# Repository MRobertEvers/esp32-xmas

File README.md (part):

# ESP32-S3 OSRS Model Renderer

ESP-IDF firmware for an **ESP32-S3** driving a **240×240 ST7789** SPI LCD. It renders an animated Old School RuneScape model in software — no GPU, no PSRAM — using **[toridraw](3rd/oldschool-clientc/3rd/toridraw)** for the raster and **[rscache](3rd/oldschool-clientc/3rd/rscache)** for the cache formats.

The model, its animation, its textures and toridraw's lookup tables are all baked into flash at build time. The device decodes nothing at boot.

Current subject: the Tree Gnome Village spirit tree (dat2 model **2851**) playing `entendseq`, the idle that fades the orbs in its branches.

For experimental relative positioning of four or more ornaments using their
existing Wi-Fi radios, see the [spatial layout module](components/xmas_spatial/README.md)
and [standalone firmware demo](examples/spatial_layout/README.md). The module
implements discovery, FTM ranging and a documented 3D solver without third-party
libraries; it is opt-in and does not start Wi-Fi in the renderer.

---

## Hardware

| LCD pin | GPIO | Notes |
|---------|------|-------|
| SCLK    | 12   | SPI clock — IOMUX pin for SPI2, which is what allows 80 MHz |
| MOSI    | 11   | SPI data — likewise IOMUX |
| CS      | −1   | Tied low on this board |
| DC      | 9    | Data/command |
| RST     | 8    | Reset |
| BLK     | 7    | Backlight, active high, driven by LEDC PWM |
| VCC     | 3.3 V | 3.3 V only |
| GND     | GND  | |

Pins are defined at the top of [`main/main.c`](main/main.c).

**No PSRAM.** It was needed once for toridraw's lookup tables; those are `const` in flash now, and so is the model. Everything left fits in internal DRAM.

### Board (`board/xmas_orn`)

KiCad 10 project.

#### Revision history

| Rev | Date | Module | Power | Outline | Notes |
|-----|------|--------|-------|---------|-------|
| 1 | June 2026 | ESP32-S3-MINI-1-N8 (8 MB flash, no PSRAM) | USB-C only | 27.5 × 39 mm | Ordered as PCBWay SMT quote W1016619ASI9; JLCPCB outputs in `production/` |
| 2 | Sept 2026 | ESP32-S3-WROOM-1-N16R8 (16 MB flash, 8 MB octal PSRAM) | USB-C or 5 V barrel jack, Schottky OR-ed | 27.5 × 41.5 mm | Jack footprint unpopulated; fresh autoroute |

#### Rev 2 changes

- **Module:** ESP32-S3-WROOM-1-N16R8 (16 MB flash, 8 MB octal PSRAM) replaces the
  ESP32-S3-MINI-1-N8. Same GPIOs as above, and none of them are the octal-PSRAM
  pins (35/36/37), so `main.c` is unchanged. The firmware still does not *need*
  PSRAM; `sdkconfig.defaults` keeps the 8 MB flash size so it also boots on rev 1.
  Build with the `sdkconfig.rev2.defaults` overlay for rev 2 boards (see below).
- **Board outline** grew from 27.5 × 39 mm to 27.5 × 41.5 mm; the four mounting
  holes did not move. The module's antenna end overhangs the bottom edge, as the
  MINI-1's did.
- **Power inputs are OR-ed.** USB-C VBUS feeds `VIN` through D3 and the DC jack
  through D4 (B5819W Schottky, SOD-123), so USB and the jack can both be plugged in
  without back-feeding each other. `VIN` goes to the TLV75733 3.3 V LDO as before.
- **J2, DC barrel jack (DC-002, 3.5 × 1.3 mm), not populated.** Footprint and
  3D model live in the project library `xmas_orn.pretty` / `xmas_orn.3dshapes`.
  The jack must be fed **5 V DC** (the LDO's absolute maximum input is 5.5 V);
  the silkscreen says so next to the opening. Pin 1 is the centre pin (`VJACK`),
  pin 2 the sleeve (GND), pin 3 the unused switch contact.
- Copper keep-out rings around the mounting holes; minimum drill lowered to
  0.2 mm for the WROOM-1 thermal vias (within JLCPCB capability).

The routing is a fresh autoroute (Freerouting) that passes DRC with the project
rules, not a hand layout.

Outputs: `board/xmas_orn/docs/` holds the schematic and layer PDFs, a copper/silk
SVG, and 3D renders of both sides
([top](board/xmas_orn/docs/xmas_orn_rev2_top.png),
[bottom](board/xmas_orn/docs/xmas_orn_rev2_bottom.png));
`board/xmas_orn/production/rev2/` holds the JLCPCB gerber/drill zip, BOM and
placement file, exported with `kicad-cli` (J2 excluded as DNP). The placement
rotations are KiCad's raw angles, not the per-package corrections the
Fabrication Toolkit plugin applies, so check the part orientation in JLCPCB's
placement preview before confirming. The files directly under `production/` are
the rev 1 outputs.

Firmware for rev 2: `sdkconfig.rev2.defaults` overlays the 16 MB flash size and
enables the octal PSRAM. The base defaults still build a firmware that runs on
both revisions.

#### Parts on hand for rev 2

The rev 2 part choices follow what was actually bought (from the order emails,
all AliExpress unless noted):

| Part | Qty | Order | Ordered | Used as |
|------|-----|-------|---------|---------|
| ESP32-S3 WROOM-1 family module, N16R8 | 5 | 8212428463925361 | 2026-06-15 | **U1.** Bare module, 16 MB flash + 8 MB PSRAM. The listing photo shows the WROOM-1 shield can; if these turn out to be the 1U (IPEX) variant the same pads apply, only the antenna overhang is unused. |
| DC-002 DC power jack, 3.5 × 1.3 mm, 3-pin | 20 | 8212428463985361 (shipped in package 8212428463965361) | 2026-06-15 | **J2**, not populated by default. Footprint from LCSC C381119 (XKB DC-002-2.0A-1.3); pin 1 centre, 2 sleeve, 3 switch. |
| ESP32-S3-MINI-1-N4R2 | 4 | 8211751284255361 | 2026-06-17 | Not used. Drop-in for the rev 1 MINI-1 footprint (4 MB flash + 2 MB PSRAM) if a rev 1 board is respun instead. |
| ESP32-S3 1.69" touch-screen dev boards | 2 | 8211746880775361 | 2026-06-17 | Not used; dev boards, not modules. |
| ESP-32S (classic ESP32) module set | 1 | 8212349322565361 | 2026-06-17 | Not used; wrong chip family. |
| AYWHP ESP32-S3 dev boards with WROOM-1-N16R8 | 3 | Amazon 114-8171301-3841008 | 2026-06-04 | Not used; dev boards. Handy for bringing up the N16R8 firmware config before rev 2 boards arrive. |
| 3.3 V / 5 V / 12 V power supply module | 1 | 8212428463975361 (same package) | 2026-06-15 | Not on the board. |

#### JLCPCB placement gotchas (learned on order W2026090908054344, 2026-09-08)

- **Rotations.** `kicad-cli` writes KiCad's raw footprint angle, but JLCPCB
  applies that angle to *its own* part model, whose 0° differs per package.
  On the first rev 2 order the 1×7 socket J1 came out vertical and the
  WROOM-1 U1 was flipped end-for-end (antenna on the board, shield hanging
  off the edge). JLCPCB's engineer corrected both before production, and the
  CPL in `production/rev2/` now carries the JLCPCB-correct angles for those
  two parts (J1 = 0, U1 = 0). Any new footprint needs the same check.
- **Always open Order History → DFM Analysis after paying** and tick
  "Show Components": that view is the engineer-adjusted placement that will
  actually be built. Verify every polarised part (diodes, LEDs, ICs, the
  module, connectors) against `docs/xmas_orn_rev2_top.png` before the SMT
  line starts. "Confirm Parts Placement" at order time makes JLCPCB wait for
  your sign-off instead.
- **Through-hole parts must be in the CPL** or JLCPCB skips them: the hub's
  jack, terminal blocks and bulk cap were missing from the SMD-only export.
  `xmas_hub/production/JLCPCB_xmas_hub_positions.csv` now lists all 60 parts
  in the five-column form (Designator, Mid X, Mid Y, Rotation, Layer);
  JLCPCB's parser rejects quoted fields, so keep footprint names out of it.
- **Part numbers.** Give JLCPCB LCSC C-numbers, not manufacturer numbers; its
  matcher fails on hyphenated MPNs. Substitutions made on that order: hub Q1
  AOD417 → AOD4185 (C400894, out of stock); ornament J1 = C22438157,
  J3 = C165948, SW1/SW2 = C231329.

#### Sourcing the rest

Everything new on rev 2 now carries an `LCSC Part #` field in the schematic and
board so an assembler can pick it up directly:

| Ref | Part | LCSC / JLCPCB | Status |
|-----|------|---------------|--------|
| U1 | ESP32-S3-WROOM-1-N16R8 | [C2913202](https://www.lcsc.com/product-detail/C2913202.html) ([DigiKey 16162642](https://www.digikey.com/en/products/detail/espressif-systems/ESP32-S3-WROOM-1-N16R8/16162642)) | 5 on hand |
| J2 | DC-002 jack (XKB DC-002-2.0A-1.3) | [C381119](https://www.lcsc.com/product-detail/C381119.html) | 20 on hand; not populated |
| D3, D4 | B5819W SL, 1 A / 40 V Schottky, SOD-123 | [C8598](https://jlcpcb.com/partdetail/9093-B5819WSL/C8598), a JLCPCB *basic* part | **Not on hand.** Needs 2 per board. |

B5819W was not in any order. It is sourced from JLCPCB's parts library as
[C8598](https://jlcpcb.com/partdetail/9093-B5819WSL/C8598) (Jiangsu Changjing
B5819W SL), a *basic* library part, so it is placed at assembly with no feeder
fee and nothing needs to be bought separately.

Nothing else on the rev 2 BOM changed from rev 1, so the rev 1 part numbers in
`production/JLCPCB_xmas_orn_bom.csv` still apply to those references.

---

### Enclosure (`board/xmas_orn/enclosure`)

A printed case for the rev 2 board plus its display, done as a **common core** (tray + snap-on
bezel) that slots into interchangeable **outers**, the default being a rounded hanging sleeve.
Parametric OpenSCAD, print-oriented STLs for the Bambu Lab A1 mini, and the core envelope /
groove interface any new outer needs are documented in
[board/xmas_orn/enclosure/README.md](board/xmas_orn/enclosure/README.md). The barrel jack and
USB-C are open through both the core and the sleeve.
Five themed outers (Captain America shield, two Spider-Man variants, Iron Man, Black Widow)
share the same pocket and export one STL per colour for the AMS lite.

The power hub gets a plainer two-part box, same toolchain, in
[board/xmas_hub/enclosure/](board/xmas_hub/enclosure/README.md): four M3 screws from below
clamp the board and the lid together, with a notch for the 12 V jack and windows for the four
arm terminals.

---

### Power hub (`board/xmas_hub`)

A second KiCad 10 project: the base-of-tree distribution board for the rev 2
jack. A 12 V / 3 A barrel supply goes in; four independently regulated and
fused **5 V / 3 A arms** come out on screw terminals, each feeding a short
cluster of ornaments through their DC-002 jacks. One TPS54302 buck and one PTC
per arm, so a fault on one arm leaves the other three running — the "star"
topology without a buck on every ornament. Design notes, BOM with LCSC numbers,
cable guidance and the generator scripts are in
[`board/xmas_hub/README.md`](board/xmas_hub/README.md); JLCPCB outputs in
`board/xmas_hub/production/`.

## Software used

| Area | Tool | Version / where | Used for |
|------|------|-----------------|----------|
| Firmware | [ESP-IDF](https://docs.espressif.com/projects/esp-idf/) | v5.1+ | `idf.py` build, flash, monitor; CMake drives the bake generators |
| Firmware | Host C compiler | any `gcc` on `PATH` (`HOST_CC` overrides) | Builds `tools/bake_model` and `tools/extract_model`, which run at build time |
| Firmware | PowerShell | `scripts/*.ps1` | The three build-time generators (`bake-model`, `gen-const-tables`, `extract-model`) |
| Firmware | [toridraw / rscache](https://github.com/MRobertEvers/oldschool-clientc) | submodule pin in `3rd/` | Software rasteriser and OSRS cache readers |
| Board | [KiCad](https://www.kicad.org/) | 10.0.6 | `board/xmas_orn` and `board/xmas_hub` schematics and layouts |
| Board | `kicad-cli` | ships with KiCad | ERC/DRC, netlist, BOM, position file, gerber/drill export, PDF/SVG/PNG renders in `docs/` |
| Board | KiCad's bundled Python (`pcbnew`) | inside the KiCad app bundle | `board/xmas_hub/scripts/gen_sch.py` / `gen_pcb.py` generate that board programmatically |
| Board | [Freerouting](https://github.com/freerouting/freerouting) | | Autorouting; both boards are fresh autoroutes that pass the project DRC |
| Board | [Fabrication Toolkit](https://github.com/bennymeg/Fabrication-Toolkit) | KiCad plugin, `fabrication-toolkit-options.json` | Rev 1 JLCPCB outputs under `production/`; rev 2 used `kicad-cli` directly |
| Enclosure | [OpenSCAD](https://openscad.org/) | 2026.09 snapshot, `brew install --cask openscad@snapshot` | `board/xmas_orn/enclosure/xmas_orn_case.scad`; `export.sh` renders the STLs and the `check_*` parts prove the fit |
| Enclosure | [trimesh](https://trimesh.org/) (optional) | `pip install trimesh numpy networkx` | Watertightness and overlap-volume checks on the exported meshes |
| Enclosure | [Bambu Studio](https://bambulab.com/en/download/studio) | | Slicing for the Bambu Lab A1 mini; the STLs are already print-oriented |

On macOS the stable `openscad` cask is disabled (Gatekeeper); use the snapshot cask. KiCad's
`kicad-cli` and Python live at `/Applications/KiCad/KiCad.app/Contents/MacOS/kicad-cli` and
`.../Contents/Frameworks/Python.framework/Versions/Current/bin/python3`. `qlmanage -t` is a
handy stand-in for `pdftoppm` when previewing the exported PDFs.

## Prerequisites

- ESP-IDF v5.1+
- A host `gcc` on `PATH` (MinGW is fine) to build the bake tools. `HOST_CC` overrides.
- **The OSRS caches**, which are *not* vendored — see below.

### Libraries: vendored as a submodule

`toridraw`, `rscache` and `toridraw_rscache` come from
[`oldschool-clientc`](https://github.com/MRobertEvers/oldschool-clientc), pinned
as a submodule at [`3rd/oldschool-clientc`](3rd/oldschool-clientc).

```powershell
git clone git@github.com:MRobertEvers/esp32-xmas.git
cd esp32-xmas
git submodule update --init --recursive
```

`--recursive` matters: the nested `OSRS-Content` submodule supplies `all.seq`,
which is where the animation frame ids and their hold times come from.

This used to be `../oldschool-clientc` — whatever happened to be checked out
next to this repo on the machine doing the build. That is not a version. The
Xtensa raster kernels this client depends on are developed in that repo, so two
working copies routinely meant two different firmwares from the same source
tree, with nothing recording the difference.

To build against a live working copy of the library instead of the pin:

```powershell
idf.py -DCLIENTC_DIR=C:\path\to\oldschool-clientc build
```

### Caches: local, not vendored

The caches are gigabytes of game data and are gitignored in *both* repos, so the
submodule carries the libraries and the configs but **no cache**. They get their
own root, defaulting to a sibling checkout:

| Variable | Default | |
|---|---|---|
| `CACHE_ROOT` | `../oldschool-clientc` | where the caches live |
| `ANIM_CACHE_DIR` | `${CACHE_ROOT}/cache.osrs239` | dat2 cache |
| `CACHE_DIR` | `${CACHE_ROOT}/cache.rs289lc` | dat1 cache |

Pointing these at the submodule would look tidier and would silently break every
fresh clone, because the directory exists and is empty.

## Build and flash

```powershell
. C:\Users\<you>\esp\esp-idf\export.ps1
idf.py set-target esp32s3
idf.py build
idf.py -p COM3 flash monitor
```

`idf.py build` runs three generators before compiling:

1. **`scripts/bake-model.ps1`** → `build/gen/xmas_baked.c`. The model, the rig, every animation frame and every texture, as `const` arrays.
2. **`scripts/gen-const-tables.ps1`** → `build/gen/toridraw_tables_precomputed.c`. toridraw's HSL palette and trigonometry, for the configured pixel format.
3. **`scripts/extract-model.ps1`** → `build/model.bin`, flashed to the `model` partition.

All three track their CMake cache variables, so changing the model re-bakes.

---

## Choosing a model and animation

```powershell
idf.py -DANIM_MODEL=2851 -DANIM_SEQ=entendseq build
```

| Variable | Default | Meaning |
|---|---|---|
| `ANIM_MODEL` | `2851` | dat2 model id |
| `ANIM_SEQ` | `entendseq` | sequence name in `all.seq` |
| `ANIM_CACHE_DIR` | `${CACHE_ROOT}/cache.osrs239` | dat2 cache |

### Pick a sequence that actually animates this model

Some sequences drive **two** models and hide whichever is not current, by collapsing every one of its vertices onto a single point. Render one model of such a pair and roughly half the frames draw nothing at all — which looks like flicker, and is the animation behaving correctly.

`pog_spirit_tree_anim` is one of these: `models=49769,49771`, cross-faded by `pog_spirit_tree_transform`. 48 of its 99 poses came out with bounds `radius 0`.

The firmware checks for this at boot and says so:

```
all 12 poses draw
```

or, if you have picked one of those sequences:

```
W: 48 of 99 poses draw nothing -- the sequence probably drives a
   second model that this one is hidden for
```

A `readyanim` has no partner: it loops, and every frame has geometry.

### A sequence can hide part of a model on purpose

Picking a sequence that animates the model is not the same as picking one that
shows all of it. Model 2851 has two idles, and `all.loc` uses them to mean
different things:

| loc | anim | orbs |
|---|---|---|
| `spirittree_big_2ops` | `entready` | hidden |
| `spirittree_big_2ops_orbs` | `entendseq` | fading |

The rig has two type-5 (transparency) groups. `entready` holds them at a
constant +16 and +32 on every frame -- and +32x8 = 256, which clamps to 255,
so the orbs are fully hidden. That is correct: that loc has no orbs.
`entendseq` ramps the second group 20 -> 6 and back and dips the first to -10,
which is the fade.

So "the orbs do not fade" had two different causes in sequence, and only the
first was a bug: the model had no face bones baked, so no type-5 op ran at all;
and then the sequence in use genuinely asked for them to be hidden.

---

## Lighting

Applied at bake time, so the device receives finished colours and never lights anything.

```
lightness = ambient + (L·N) / (attenuation × face_count)
```

That result then *scales* each face's own base lightness, clamped to `[2,126]`.

| Variable | Default | Effect |
|---|---|---|
| `LIGHT_AMBIENT` | `128` | The floor. Slides the whole model brighter or darker. |
| `LIGHT_ATTENUATION` | `192` | **The contrast knob.** Divides the directional term, so *lower* is a wider swing. Reference is 768. |
| `LIGHT_GAMMA` | `1.0` | Re-curves the distribution. A **brightness** knob — see below. |
| `LIGHT_DIR` | `-50,-10,-50` | Light vector. |

Every bake prints what it did:

```
lighting: ambient 128, attenuation 192, dir -50,-10,-50
  p10 15, p50 35, p90 120 (inner spread 105)
  lightness 2..126 (spread 124), mean 49, 7% on the clamps
```

**Read the inner spread, not the range.** The min and max are two faces; p10–p90 is the thousand in between, and that is what the eye reads as contrast. Measured on model 2851:

| ambient | attenuation | gamma | inner spread | mean | clipped |
|---|---|---|---|---|---|
| 64 | 768 (reference) | 1.0 | — | 24 | 0% |
| 96 | 384 | 1.0 | 69 | 37 | 0% |
| 96 | 192 | 1.0 | 88 | 38 | 2% |
| 96 | 192 | 0.8 | 87 | 46 | 2% |
| **128** | **192** | **1.0** | **105** | **49** | **7%** |
| 96 | 128 | 1.0 | 108 | 39 | 17% |

`attenuation` is the only knob that moves the inner spread. **Gamma does not add contrast** — measured, it moved the mean 37 → 73 while *shrinking* inner spread 69 → 55. It is there for a model that is too dark, not one that is too flat.

`clipped` is the share of face corners pinned at 2 or 126, which have lost their shading. 7% is the price of the current default; `-DLIGHT_AMBIENT=96 -DLIGHT_ATTENUATION=192 -DLIGHT_GAMMA=0.8` is the same contrast at 2%.

---

## Animation timing

Sequences run on the reference client's **50 Hz** cycle, and each frame carries its own hold time.

That hold time lives **only in the seq config** — `frame=<packed id>,<ticks>` in `all.seq`. The frame archive does not carry it, so nothing downstream can recover it if the packer drops it. `entendseq` holds its 18 frames for 4-5 ticks: about 90 ms a pose. (`entready`, the other idle for this rig, holds for 21.)

The render loop derives the animation phase from `esp_timer` rather than counting passes, so playback rate does not change when render cost does. The boot log reports a measured rate:

```
frame 4: 44.2 fps, 2.0 poses/s  visible=1  7794 px  anim 1.06 ms  raster 5.74 ms  blit 0.25 ms
```

Both numbers are per wall-clock second. Counting frames and multiplying by an assumed period produces a rate that lies whenever the loop misses its period.

---

## Textures

A textured face carries a texture **id**, not texels, and toridraw's texture map starts empty. **Its raster silently skips any face whose id is not registered** — no error, no gap in the depth order. An unregistered texture is indistinguishable from a model with no textured faces.

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
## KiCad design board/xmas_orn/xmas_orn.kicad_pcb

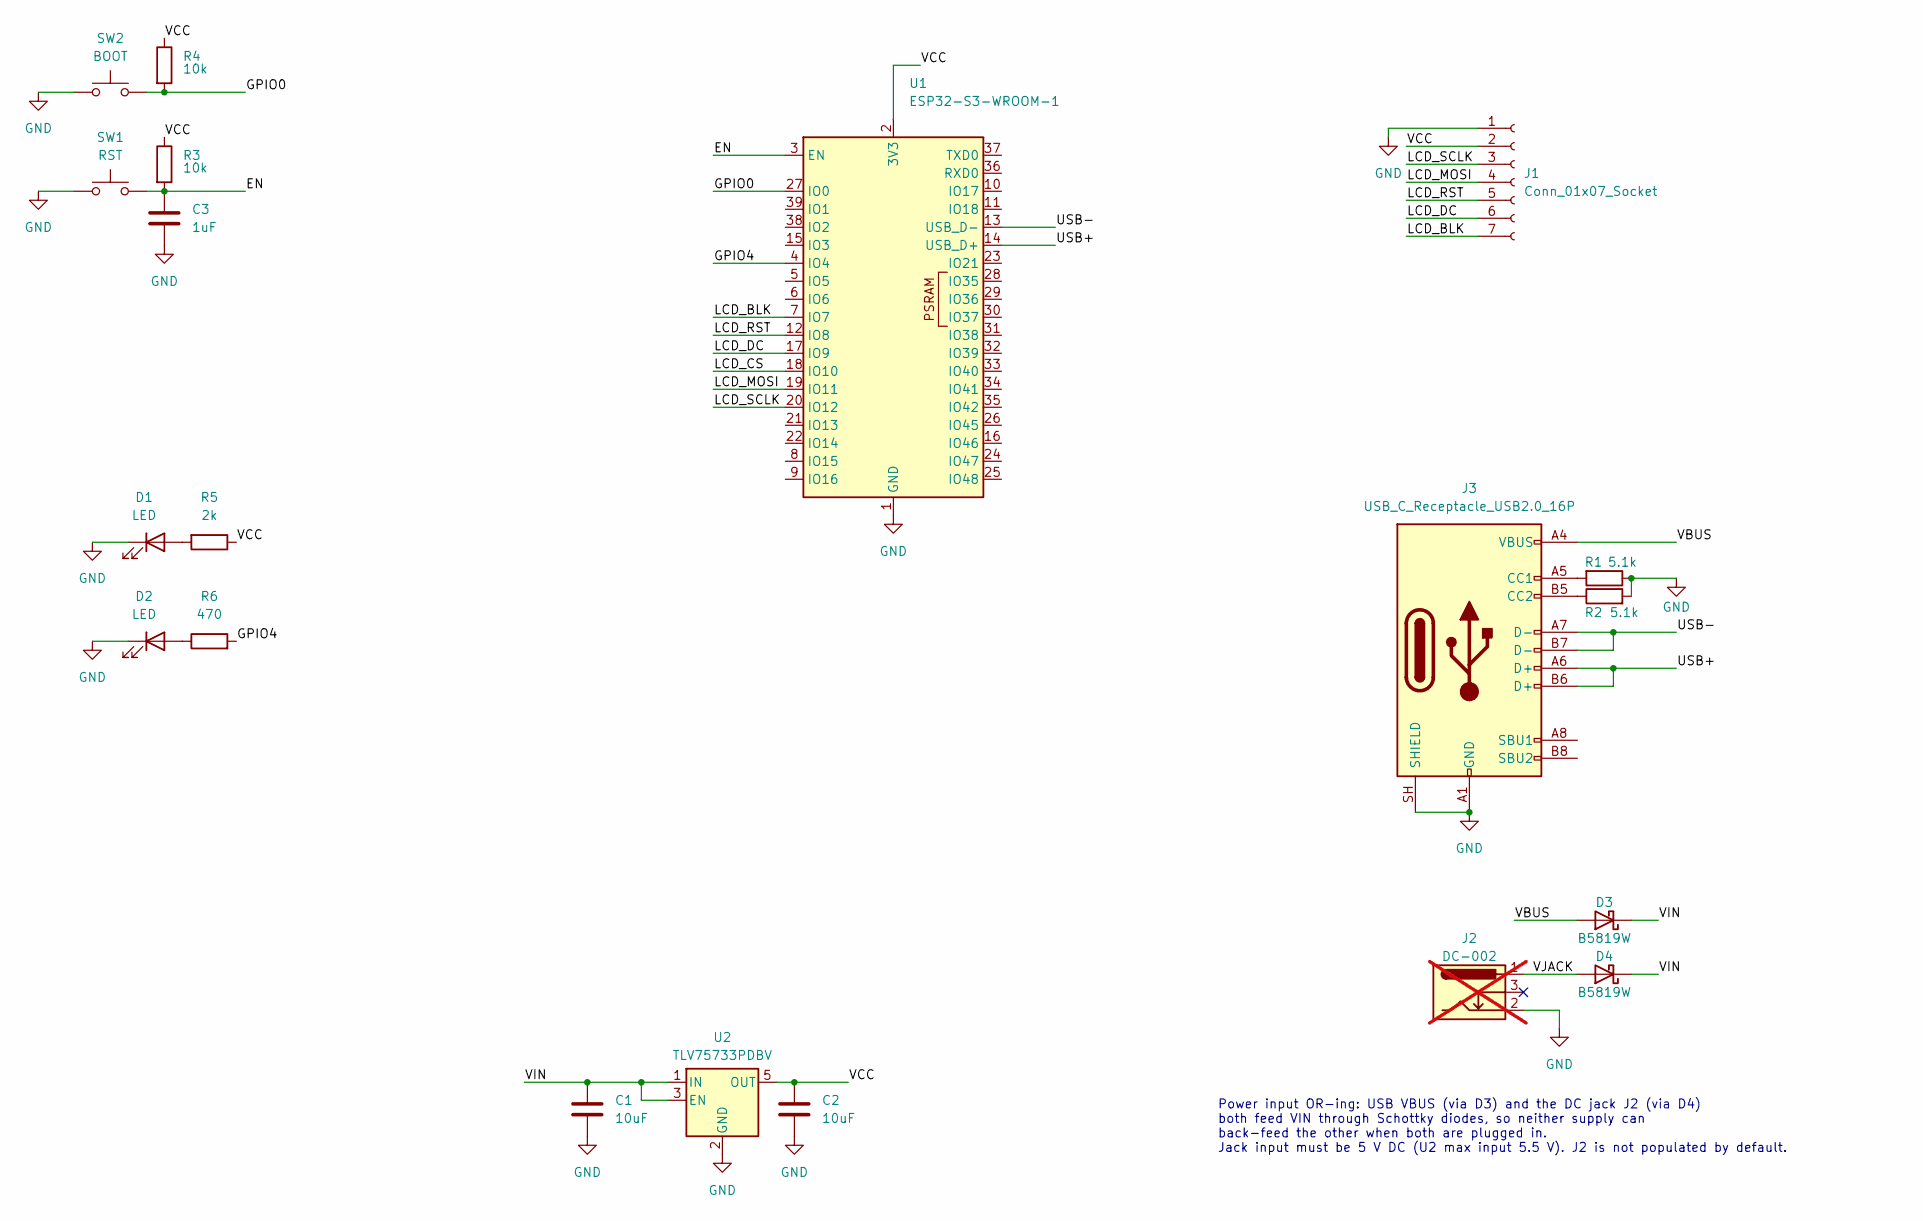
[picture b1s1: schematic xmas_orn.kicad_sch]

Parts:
C1, C2: 10uF; C_0805_2012Metric; MPN CL21A106KOQNNNE
C3: 1uF; C_0603_1608Metric; MPN CL10A105KA8NNNC
D1, D2: LED; LED_0603_1608Metric; MPN 19-217/R6C-AL1M2VY/6T
D3, D4: B5819W; D_SOD-123; MPN B5819W; LCSC Part # C8598
J1: Conn_01x07_Socket; PinSocket_1x07_P2.54mm_Vertical; MPN HX PM2.54-1x7P ZC-Y
J2: DC-002; DC-002_BarrelJack_3.5x1.3mm_Horizontal; MPN DC-002; LCSC Part # C381119; not fitted
J3: USB_C_Receptacle_USB2.0_16P; USB_C_Receptacle_HRO_TYPE-C-31-M-12; MPN TYPE-C-31-M-12
R1, R2: 5.1k; R_0603_1608Metric; MPN RC0603FR-075K1L
R3, R4: 10k; R_0603_1608Metric; MPN AC0603JR-0710KL
R5: 2k; R_0603_1608Metric; MPN RC0603JR-072KL
R6: 470; R_0603_1608Metric; MPN RC0603FR-07470RL
SW1: RST; SW_SPST_B3U-1000P; MPN B3U-1000P
SW2: BOOT; SW_SPST_B3U-1000P; MPN B3U-1000P
U1: ESP32-S3-WROOM-1; MPN ESP32-S3-WROOM-1-N16R8; LCSC Part # C2913202
U2: TLV75733PDBV; SOT-23-5; MPN TLV75733PDBVR-MS

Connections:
/EN: C3.1, R3.2, SW1.2, U1.3 (EN)
/GPIO0: R4.2, SW2.2, U1.27 (IO0)
/GPIO4: R6.2, U1.4 (IO4)
/LCD_BLK: J1.7, U1.7 (IO7)
/LCD_CS: U1.18 (IO10)
/LCD_DC: J1.6, U1.17 (IO9)
/LCD_MOSI: J1.4, U1.19 (IO11)
/LCD_RST: J1.5, U1.12 (IO8)
/LCD_SCLK: J1.3, U1.20 (IO12)
/USB+: J3.A6 (D+), J3.B6 (D+), U1.14 (USB_D+)
/USB-: J3.A7 (D-), J3.B7 (D-), U1.13 (USB_D-)
/VBUS: D3.2 (A), J3.A4 (VBUS), J3.A9 (VBUS), J3.B4 (VBUS), J3.B9 (VBUS)
/VCC: C2.1, J1.2, R3.1, R4.1, R5.1, U1.2 (3V3), U2.5 (OUT)
/VIN: C1.1, D3.1 (K), D4.1 (K), U2.1 (IN), U2.3 (EN)
/VJACK: D4.2 (A), J2.1
GND: C1.2, C2.2, C3.2, D1.1 (K), D2.1 (K), J1.1, J2.2, J3.A1 (GND), J3.A12 (GND), J3.B1 (GND), J3.B12 (GND), J3.SH (SHIELD), R1.1, R2.2, SW1.1, SW2.1, U1.1 (GND), U1.40 (GND), U1.41 (GND), U2.2 (GND)
unnamed: D1.2 (A), R5.2
unnamed: D2.2 (A), R6.1
unnamed: J3.A5 (CC1), R1.2
unnamed: J3.B5 (CC2), R2.1

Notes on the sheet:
Power input OR-ing: USB VBUS (via D3) and the DC jack J2 (via D4) both feed VIN through Schottky diodes, so neither supply can back-feed the other when both are plugged in. Jack input must be 5 V DC (U2 max input 5.5 V). J2 is not populated by default.

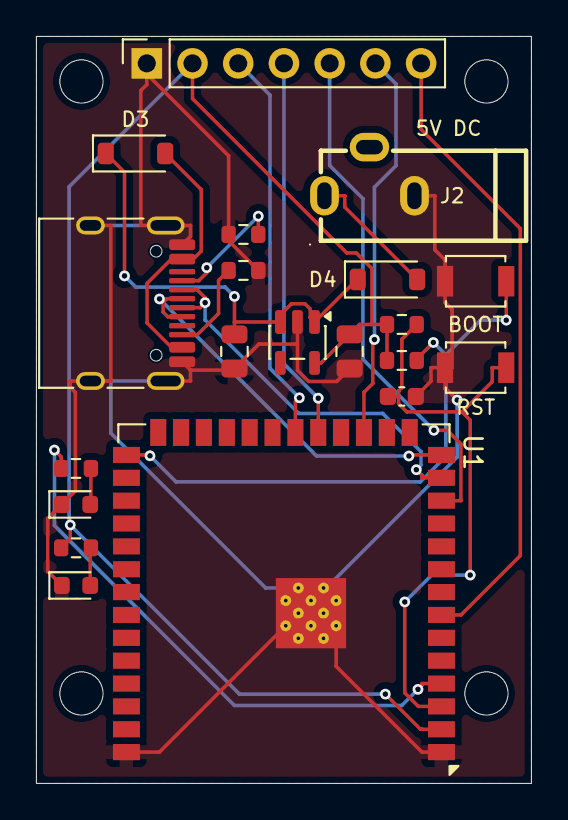
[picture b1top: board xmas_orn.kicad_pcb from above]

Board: 2 copper layers, 27.5 x 41.5 mm, 20 parts (0 on the bottom side), 19 nets.

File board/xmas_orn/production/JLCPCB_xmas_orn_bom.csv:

Designator,Footprint,Quantity,Value,LCSC Part #
"C1, C2",0805,2,10uF,CL21A106KOQNNNE
C3,0603,1,1uF,CL10A105KA8NNNC
"D1, D2",0603,2,LED,19-217/R6C-AL1M2VY/6T
J1,PinSocket_1x07_P2.54mm_Vertical,1,Conn_01x07_Socket,HX PM2.54-1x7P ZC-Y
J3,USB_C_Receptacle_HRO_TYPE-C-31-M-12,1,USB_C_Receptacle_USB2.0_16P,TYPE-C-31-M-12
"R1, R2",0603,2,5.1k,RC0603FR-075K1L
"R3, R4",0603,2,10k,AC0603JR-0710KL
R5,0603,1,2k,RC0603JR-072KL
R6,0603,1,470,RC0603FR-07470RL
SW1,SW_SPST_B3U-1000P,1,RST,B3U-1000P
SW2,SW_SPST_B3U-1000P,1,BOOT,B3U-1000P
U1,ESP32-S2-MINI-1,1,ESP32-S3-MINI-1,ESP32-S3-MINI-1-N8
U2,SOT-23-5,1,TLV75733PDBV,TLV75733PDBVR-MS

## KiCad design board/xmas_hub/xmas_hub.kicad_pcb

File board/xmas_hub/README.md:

# xmas_hub — 12 V to 4 × 5 V star power hub

Second board in this repo. One of these sits at the base of the tree; a 12 V
barrel supply goes in, four independently regulated and fused 5 V "arms" come
out on screw terminals, and each arm feeds a short cluster of 3–4 `xmas_orn`
ornaments through their DC‑002 (3.5 × 1.3 mm) barrel jacks.

## Why per-arm regulators

Distributing 12 V and converting near the load is what makes the star
topology work at hobby wire gauges: the trunk carries a quarter of the current
it would at 5 V, and every arm is its own 5 V domain. A short or overload on
one arm drops that arm's PTC / that buck's hiccup limit, and the other three
keep running. "Isolated" here means independently regulated and fused, not
galvanically isolated — all arms share ground.

## Circuit

| Block | Parts | Notes |
|---|---|---|
| Input | J1 DC‑005 5.5 × 2.1 mm, centre + | Flush with the left board edge. Project footprint in `xmas_hub.pretty`: the DC‑005 has its **sleeve** on the lateral pin and the **switch** in line with the centre pin, the opposite of KiCad's generic `BarrelJack_Horizontal`, which would have put GND on the contact that opens when a plug goes in. |
| Input protection | F1 5 A PTC (2920), D1 SMAJ15A TVS, Q1 AOD417 P‑FET + R1 100k | Q1 sits in the high side with its body diode toward the load: ~30 mV drop at 3 A instead of a Schottky's 0.5 V. On a reversed supply Q1 blocks and D1 conducts forward so F1 trips. |
| Bulk | C1 100 µF 25 V radial, 6.3 mm / 2.5 mm pitch | On the +12V bus |
| Indicator | D2 red + R2 2.2k | 12 V present |
| Arm ×4 | U TPS54302, L 10 µH (Sunlord MWSA0804S‑100MT), Cin 10 µF, Cboot 100 nF, Cout 2 × 22 µF, R 100k / 13.7k, Cff 75 pF | TI's 5 V / 3 A reference circuit from the datasheet (SLVSDG6), with the bottom divider resistor changed from 13.3k to the stocked 13.7k: Vout = 0.596 V × (1 + 100/13.7) = 4.95 V. That is inside USB tolerance and leaves ~1 V of headroom over the ornament's Schottky + 3.3 V LDO even after cable drop. EN is left floating: the part has an internal pull‑up and its own VIN UVLO. |
| Arm output | F 2.6 A PTC (1812), green LED + 1k, 5.08 mm screw terminal | Pin 1 (marked `+`) is +5 V, pin 2 is GND |
| Test points | TP1 +12V, TP2 GND | |

Budget: an ornament is ~0.4 A typical (ESP32‑S3 plus backlight, more with
Wi‑Fi). Twelve of them is ~25 W, so a **12 V / 3 A adapter** is the sensible
supply; each arm can deliver up to 3 A but the input PTC and the adapter cap
the total. The board is designed for 12 V only: Q1's Vgs rating and D1's 15 V
standoff both assume it.

## Layout

80 × 66 mm, two layers, 1 oz. Ground pours on both sides, stitched under each
buck. Switch nodes are short and wide; the feedback sense runs back along the
bottom of each row from the output capacitors, away from the inductor. M3 holes
in the corners.

Copper widths were sized with IPC‑2221 for 1 oz outer copper at a 10 °C rise
(0.5 mm ≈ 1.45 A, 1.2 mm ≈ 2.7 A, 2 mm ≈ 4 A, 3 mm ≈ 5.3 A; a 0.4 mm‑drill via
≈ 1.1 A):

| Net | Current | Copper |
|---|---|---|
| Jack → F1 → D1 → Q1 → bus | up to the 5 A PTC | 3.0 mm |
| +12V bus | total input, ≤5 A | 3.0 mm |
| Per‑arm 12 V feed into Cin | ~1.4 A avg at 3 A out | 1.2 mm, 0.6 mm stub into the VIN pin |
| SW node | 3 A pulsed | 1.5 mm, 0.7 mm at the SOT‑23 pin |
| 5V out (L → Cout → PTC) and ARM (PTC → terminal) | 3 A | 2.0 mm |
| IC GND pin (low‑side return, ~1.8 A avg) | | 0.6 mm to two 0.8/0.4 mm vias |
| Cin GND | ~1.5 A ripple | 0.8 mm to two 0.8/0.4 mm vias |
| Cout GND | ripple | 0.8 mm to one 0.8/0.4 mm via each |
| Terminal and jack GND pins | 3 A / 5 A | through‑hole into both planes |
| FB sense, boot, LEDs, test points | signal | 0.25–0.5 mm |

## Arm cables

Each arm is a twin‑lead harness with a 3.5 × 1.3 mm barrel plug (centre
positive) at each ornament. Use 20–22 AWG for the run from the hub to the
cluster and keep the runs short — that is the point of the star. The
ornament's J2 jack is DNP by default; populate it on ornaments that will be
fed from the hub.

## Enclosure

[`enclosure/`](enclosure/) holds a printed two-part box: base with standoffs, lid with
screw bosses, four M3 x 16 screws from underneath doing double duty as board and lid
fixings. Notch for the 12 V jack on the left, four wire windows for the arm terminals on
the right, LED sight holes and vents in the lid. STLs are print-oriented for the A1 mini.
See [enclosure/README.md](enclosure/README.md).

## Documents

`docs/` has the rev 1 schematic and the top and bottom layer plots as PDFs,
same naming as the ornament board, plus PNG renders: the
[schematic](docs/xmas_hub_rev1_schematic.png), and
[top](docs/xmas_hub_rev1_top.png), [bottom](docs/xmas_hub_rev1_bottom.png) and
[angled](docs/xmas_hub_rev1_iso.png) 3D views of the board. `docs/datasheets/` holds the datasheets the
design was checked against: TPS54302, AOD417, SMAJ15A, both PTCs, the DC‑005
jack (whose drawing is where the pin mapping above comes from), the KF301
terminal, the electrolytic and the Sunlord MWSA inductor series.

## Ordering (JLCPCB)

`production/` holds gerbers + drills (`JLCPCB_xmas_hub.zip`), a position file
and a BOM. Every line is sourced on LCSC; the `LCSC Part #` field is on each
symbol and footprint, so the Fabrication Toolkit picks it up too.

| Part | Value | MPN | LCSC |
|---|---|---|---|
| U1–U4 | buck | TPS54302DDCR | C311983 |
| L1–L4 | 10 µH | Sunlord MWSA0804S‑100MT | C17700171 |
| Q1 | P‑FET | AOD417 | C131415 |
| D1 | TVS | SMAJ15A (Littelfuse) | C148216 |
| F1 | 5 A PTC | 2920L500/16MR | C207091 |
| F11–F41 | 2.6 A PTC | SMD1812P260TF/16 | C438899 |
| J1 | barrel | DC‑005 (2.0 mm pin) | C16214 |
| J2–J5 | terminal | KF301‑5.0‑2P | C474881 |
| C1 | 100 µF 25 V | Chengx GR107V025E11RR0VH4FP0 | C44601 |
| C11–C41 | 10 µF 25 V X7R 1206 | CL31B106KAHNNNE | C14860 |
| C12–C42 | 100 nF 50 V X7R 0603 | CL10B104KB8NNNC | C1591 |
| C13/C14 … | 22 µF 10 V X5R 0805 | CL21A226MPQNNNE | C29277 |
| C15–C45 | 75 pF C0G 0603 | CC0603JRNPO9BN750 | C282074 |
| R1, R11–R41 | 100k | 0603WAF1003T5E | C25803 |
| R12–R42 | 13.7k | RC0603FR‑0713K7L | C482771 |
| R13–R43 | 1k | 0603WAF1001T5E | C21190 |
| R2 | 2.2k | 0603WAF2201T5E | C4190 |
| D2 | red 0603 | KT‑0603R | C2286 |
| D11–D41 | green 0603 | KT‑0603G | C12624 |

The KF301 is 5.0 mm pitch on a 5.08 mm footprint; 0.08 mm over two pins is
nothing. Codes were checked against LCSC/JLCPCB listings on 2026‑09‑06; stock
moves, so let JLC substitute equivalents for the passives if one is out.

## Regenerating

The schematic and PCB were bootstrapped by the scripts in `scripts/`:

```powershell
python3 scripts/gen_sch.py                      # -> xmas_hub.kicad_sch
kicad-cli sch export netlist --format kicadxml -o scripts/hub.xml xmas_hub.kicad_sch
<kicad python> scripts/gen_pcb.py               # -> xmas_hub.kicad_pcb
```

`<kicad python>` is the interpreter inside the KiCad app bundle (it has the
`pcbnew` module). The scripts are one‑shot generators: they **overwrite** the
files, so once the design is edited in KiCad, leave them alone or treat them as
a record of how it was laid out. ERC and DRC (with schematic parity) pass with
`kicad-cli`; the only reports left are "library not configured" notes from
running headless.

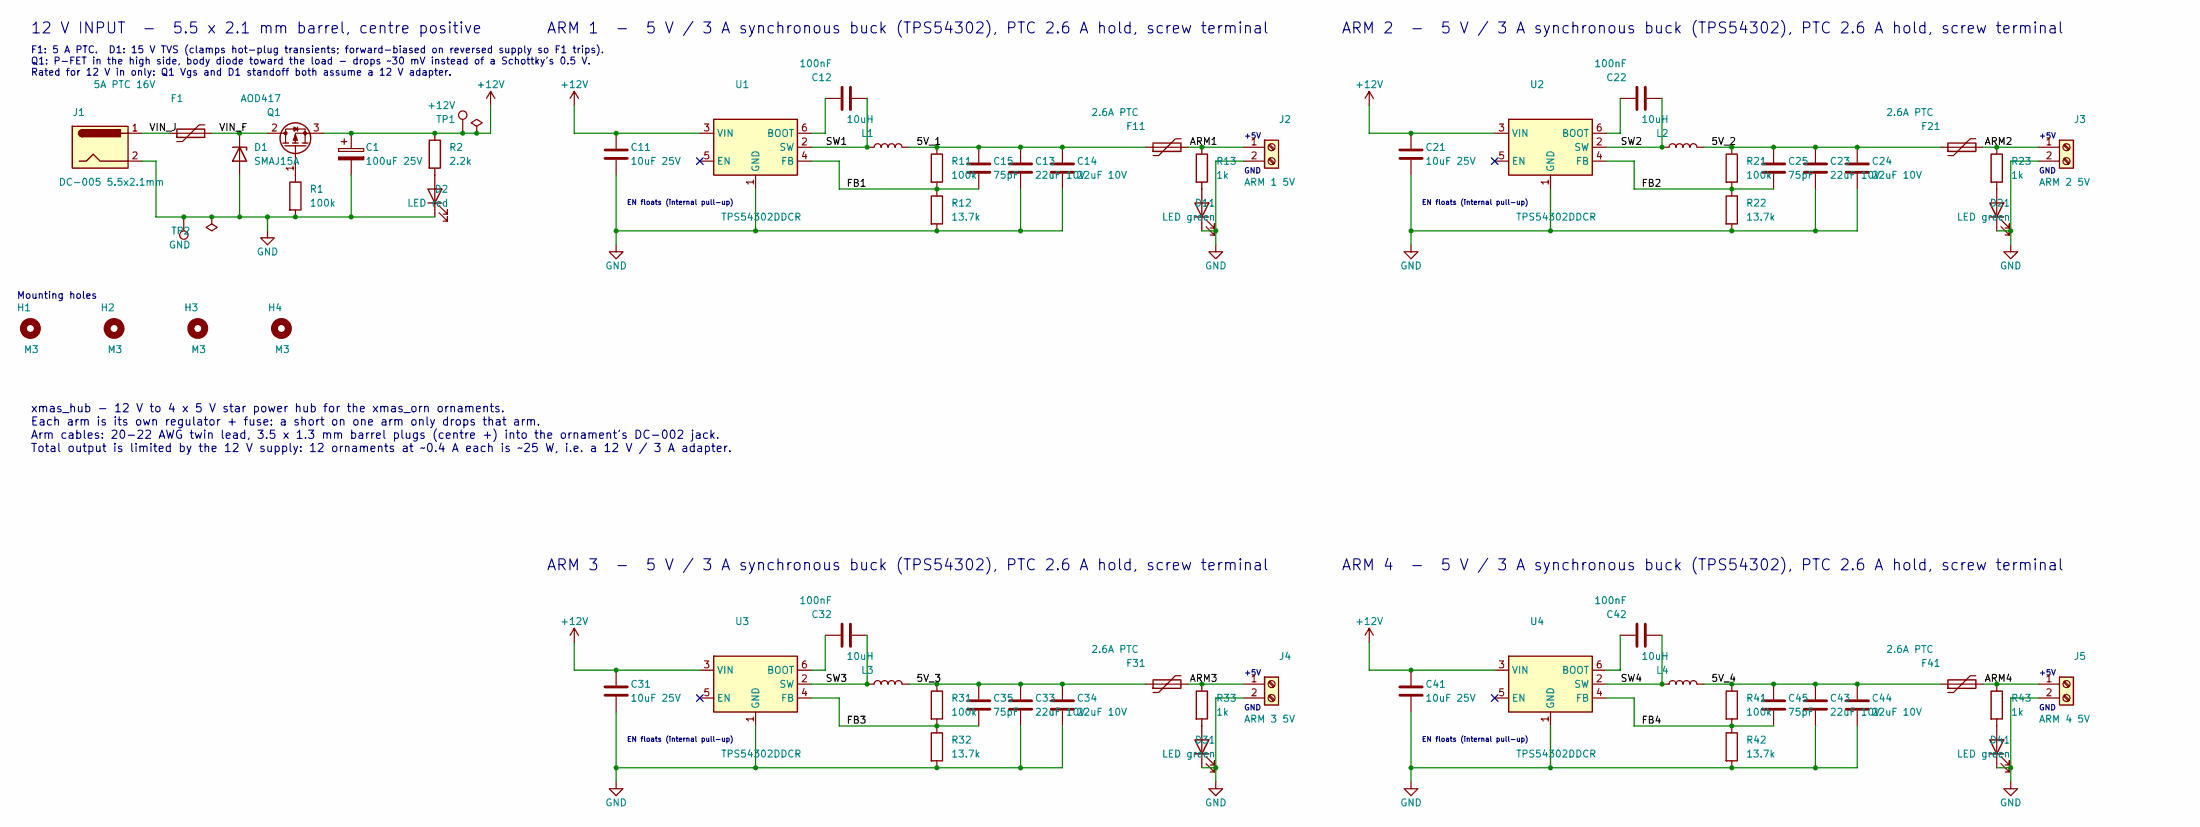
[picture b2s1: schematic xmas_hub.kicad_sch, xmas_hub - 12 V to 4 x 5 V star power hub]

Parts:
C1: 100uF 25V; CP_Radial_D6.3mm_P2.50mm; MPN GR107V025E11RR0VH4FP0; LCSC Part # C44601
C11, C21, C31, C41: 10uF 25V; C_1206_3216Metric; MPN CL31B106KAHNNNE; LCSC Part # C14860
C12, C22, C32, C42: 100nF; C_0603_1608Metric; MPN CL10B104KB8NNNC; LCSC Part # C1591
C13, C14, C23, C24, C33, C34, C43, C44: 22uF 10V; C_0805_2012Metric; MPN CL21A226MPQNNNE; LCSC Part # C29277
C15, C25, C35, C45: 75pF; C_0603_1608Metric; MPN CC0603JRNPO9BN750; LCSC Part # C282074
D1: SMAJ15A; D_SMA; MPN SMAJ15A; LCSC Part # C148216
D2: LED red; LED_0603_1608Metric; MPN KT-0603R; LCSC Part # C2286
D11, D21, D31, D41: LED green; LED_0603_1608Metric; MPN KT-0603G; LCSC Part # C12624
F1: 5A PTC 16V; Fuse_2920_7451Metric; MPN 2920L500/16MR; LCSC Part # C207091
F11, F21, F31, F41: 2.6A PTC; Fuse_1812_4532Metric; MPN SMD1812P260TF/16; LCSC Part # C438899
H1, H2, H3, H4: M3; MountingHole_3.2mm_M3
J1: DC-005 5.5x2.1mm; DC-005_BarrelJack_5.5x2.1mm_Horizontal; MPN DC-005 (2.0 mm pin); LCSC Part # C16214
J2: ARM 1 5V; TerminalBlock_Phoenix_MKDS-1,5-2-5.08_1x02_P5.08mm_Horizont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; MPN KF301-5.0-2P; LCSC Part # C474881
J3: ARM 2 5V; TerminalBlock_Phoenix_MKDS-1,5-2-5.08_1x02_P5.08mm_Horizont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; MPN KF301-5.0-2P; LCSC Part # C474881
J4: ARM 3 5V; TerminalBlock_Phoenix_MKDS-1,5-2-5.08_1x02_P5.08mm_Horizont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; MPN KF301-5.0-2P; LCSC Part # C474881
J5: ARM 4 5V; TerminalBlock_Phoenix_MKDS-1,5-2-5.08_1x02_P5.08mm_Horizont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; MPN KF301-5.0-2P; LCSC Part # C474881
L1, L2, L3, L4: 10uH; L_Sunlord_MWSA0804S; MPN MWSA0804S-100MT; LCSC Part # C17700171
Q1: AOD417; TO-252-2; MPN AOD417; LCSC Part # C131415
R1, R11, R21, R31, R41: 100k; R_0603_1608Metric; MPN 0603WAF1003T5E; LCSC Part # C25803
R2: 2.2k; R_0603_1608Metric; MPN 0603WAF2201T5E; LCSC Part # C4190
R12, R22, R32, R42: 13.7k; R_0603_1608Metric; MPN RC0603FR-0713K7L; LCSC Part # C482771
R13, R23, R33, R43: 1k; R_0603_1608Metric; MPN 0603WAF1001T5E; LCSC Part # C21190
TP1: +12V; TestPoint_Pad_D1.5mm
TP2: GND; TestPoint_Pad_D1.5mm
U1, U2, U3, U4: TPS54302DDCR; SOT-23-6; MPN TPS54302DDCR; LCSC Part # C311983

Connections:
+12V: C1.1, C11.1, C21.1, C31.1, C41.1, Q1.3 (S), R2.1, TP1.1, U1.3 (VIN), U2.3 (VIN), U3.3 (VIN), U4.3 (VIN)
/5V_1: C13.1, C14.1, C15.1, F11.1, L1.2, R11.1
/5V_2: C23.1, C24.1, C25.1, F21.1, L2.2, R21.1
/5V_3: C33.1, C34.1, C35.1, F31.1, L3.2, R31.1
/5V_4: C43.1, C44.1, C45.1, F41.1, L4.2, R41.1
/ARM1: F11.2, J2.1, R13.1
/ARM2: F21.2, J3.1, R23.1
/ARM3: F31.2, J4.1, R33.1
/ARM4: F41.2, J5.1, R43.1
/FB1: C15.2, R11.2, R12.1, U1.4 (FB)
/FB2: C25.2, R21.2, R22.1, U2.4 (FB)
/FB3: C35.2, R31.2, R32.1, U3.4 (FB)
/FB4: C45.2, R41.2, R42.1, U4.4 (FB)
/SW1: C12.2, L1.1, U1.2 (SW)
/SW2: C22.2, L2.1, U2.2 (SW)
/SW3: C32.2, L3.1, U3.2 (SW)
/SW4: C42.2, L4.1, U4.2 (SW)
/VIN_F: D1.1 (K), F1.2, Q1.2 (D)
/VIN_J: F1.1, J1.1
GND: C1.2, C11.2, C13.2, C14.2, C21.2, C23.2, C24.2, C31.2, C33.2, C34.2, C41.2, C43.2, C44.2, D1.2 (A), D2.1 (K), D11.1 (K), D21.1 (K), D31.1 (K), D41.1 (K), J1.2, J2.2, J3.2, J4.2, J5.2, R1.2, R12.2, R22.2, R32.2, R42.2, TP2.1, U1.1 (GND), U2.1 (GND), U3.1 (GND), U4.1 (GND)
unnamed: D2.2 (A), R2.2
unnamed: D11.2 (A), R13.2
unnamed: D21.2 (A), R23.2
unnamed: D31.2 (A), R33.2
unnamed: D41.2 (A), R43.2
unnamed: Q1.1 (G), R1.1
unnamed: C12.1, U1.6 (BOOT)
unnamed: C22.1, U2.6 (BOOT)
unnamed: C32.1, U3.6 (BOOT)
unnamed: C42.1, U4.6 (BOOT)

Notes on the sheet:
12 V INPUT - 5.5 x 2.1 mm barrel, centre positive
F1: 5 A PTC. D1: 15 V TVS (clamps hot-plug transients; forward-biased on reversed supply so F1 trips). Q1: P-FET in the high side, body diode toward the load - drops ~30 mV instead of a Schottky's 0.5 V. Rated for 12 V in only: Q1 Vgs and D1 standoff both assume a 12 V adapter.
Mounting holes
ARM 1 - 5 V / 3 A synchronous buck (TPS54302), PTC 2.6 A hold, screw terminal
EN floats (internal pull-up)
+5V
GND
ARM 2 - 5 V / 3 A synchronous buck (TPS54302), PTC 2.6 A hold, screw terminal
ARM 3 - 5 V / 3 A synchronous buck (TPS54302), PTC 2.6 A hold, screw terminal
ARM 4 - 5 V / 3 A synchronous buck (TPS54302), PTC 2.6 A hold, screw terminal
xmas_hub - 12 V to 4 x 5 V star power hub for the xmas_orn ornaments. Each arm is its own regulator + fuse: a short on one arm only drops that arm. Arm cables: 20-22 AWG twin lead, 3.5 x 1.3 mm barrel plugs (centre +) into the ornament's DC-002 jack. Total output is limited by the 12 V supply: 12 o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

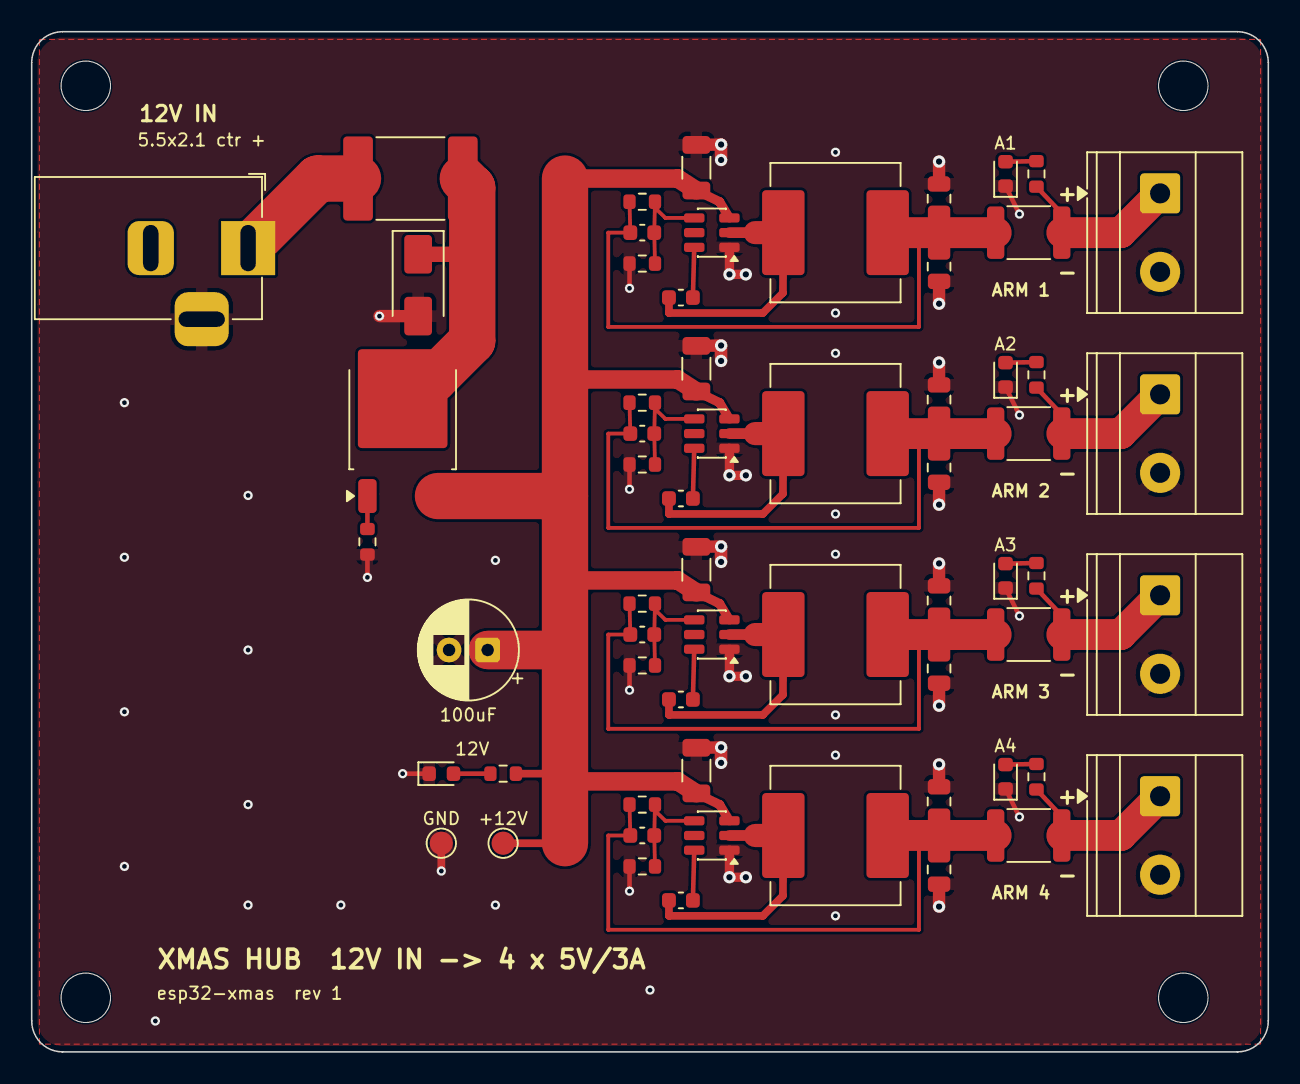
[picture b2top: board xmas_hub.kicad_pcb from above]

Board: 2 copper layers, 80.0 x 66.0 mm, 66 parts (0 on the bottom side), 30 nets.

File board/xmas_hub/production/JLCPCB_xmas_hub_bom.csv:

"Designator","Value","Footprint","MPN","LCSC Part #","Description"
"C1","100uF 25V","Capacitor_THT:CP_Radial_D6.3mm_P2.50mm","GR107V025E11RR0VH4FP0","C44601","Electrolytic bulk capacitor 100 uF 25 V 105C, 6.3 x 11 mm radial, 2.5 mm pitch"
"C11,C21,C31,C41","10uF 25V","Capacitor_SMD:C_1206_3216Metric","CL31B106KAHNNNE","C14860","Input decoupling, X7R 25 V 1206"
"C12,C22,C32,C42","100nF","Capacitor_SMD:C_0603_1608Metric","CL10B104KB8NNNC","C1591","Bootstrap capacitor, X7R 50 V"
"C13,C14,C23,C24,C33,C34,C43,C44","22uF 10V","Capacitor_SMD:C_0805_2012Metric","CL21A226MPQNNNE","C29277","Output capacitor, X5R 10 V 0805"
"C15,C25,C35,C45","75pF","Capacitor_SMD:C_0603_1608Metric","CC0603JRNPO9BN750","C282074","Feed-forward capacitor across the top FB resistor, C0G"
"D1","SMAJ15A","Diode_SMD:D_SMA","SMAJ15A","C148216","TVS diode 15 V standoff, 400 W, SMA (unidirectional); cathode to +12V"
"D2","LED red","LED_SMD:LED_0603_1608Metric","KT-0603R","C2286","12 V present indicator, red 0603"
"D11,D21,D31,D41","LED green","LED_SMD:LED_0603_1608Metric","KT-0603G","C12624","Arm live indicator, green 0603"
"F1","5A PTC 16V","Fuse:Fuse_2920_7451Metric","2920L500/16MR","C207091","Resettable PTC fuse, 5 A hold, 16 V, 2920"
"F11,F21,F31,F41","2.6A PTC","Fuse:Fuse_1812_4532Metric","SMD1812P260TF/16","C438899","Resettable PTC fuse 2.6 A hold, 16 V, 1812"
"J1","DC-005 5.5x2.1mm","xmas_hub:DC-005_BarrelJack_5.5x2.1mm_Horizontal","DC-005 (2.0 mm pin)","C16214","DC barrel jack 5.5 x 2.1 mm, DC-005 style, centre positive; pin 1 centre, pin 2 sleeve, pin 3 switch (unused)"
"J2","ARM 1 5V","TerminalBlock_Phoenix:TerminalBlock_Phoenix_MKDS-1,5-2-5.08_1x02_P5.08mm_Horizontal","KF301-5.0-2P","C474881","Screw terminal 2-pin 5.08 mm, 5 V arm 1 out: pin 1 = +5 V, pin 2 = GND"
"J3","ARM 2 5V","TerminalBlock_Phoenix:TerminalBlock_Phoenix_MKDS-1,5-2-5.08_1x02_P5.08mm_Horizontal","KF301-5.0-2P","C474881","Screw terminal 2-pin 5.08 mm, 5 V arm 2 out: pin 1 = +5 V, pin 2 = GND"
"J4","ARM 3 5V","TerminalBlock_Phoenix:TerminalBlock_Phoenix_MKDS-1,5-2-5.08_1x02_P5.08mm_Horizontal","KF301-5.0-2P","C474881","Screw terminal 2-pin 5.08 mm, 5 V arm 3 out: pin 1 = +5 V, pin 2 = GND"
"J5","ARM 4 5V","TerminalBlock_Phoenix:TerminalBlock_Phoenix_MKDS-1,5-2-5.08_1x02_P5.08mm_Horizontal","KF301-5.0-2P","C474881","Screw terminal 2-pin 5.08 mm, 5 V arm 4 out: pin 1 = +5 V, pin 2 = GND"
"L1,L2,L3,L4","10uH","Inductor_SMD:L_Sunlord_MWSA0804S","MWSA0804S-100MT","C17700171","Shielded power inductor 10 uH, Isat 7 A, Irms 5.5 A, 59 mOhm, 8x8x4 mm"
"Q1","AOD417","Package_TO_SOT_SMD:TO-252-2","AOD417","C131415","P-MOSFET -30 V, 25 A, 10 mOhm, DPAK; reverse polarity protection"
"R1,R11,R21,R31,R41","100k","Resistor_SMD:R_0603_1608Metric","0603WAF1003T5E","C25803","Feedback divider, top (0603 1%),Q1 gate pull-down (0603 1%)"
"R2","2.2k","Resistor_SMD:R_0603_1608Metric","0603WAF2201T5E","C4190","12 V indicator LED series resistor (0603 1%)"
"R12,R22,R32,R42","13.7k","Resistor_SMD:R_0603_1608Metric","RC0603FR-0713K7L","C482771","Feedback divider, bottom: Vout = 0.596 V x (1 + 100k/13.7k) = 4.95 V (0603 1%)"
"R13,R23,R33,R43","1k","Resistor_SMD:R_0603_1608Metric","0603WAF1001T5E","C21190","Arm LED series resistor (0603 1%)"
"U1,U2,U3,U4","TPS54302DDCR","Package_TO_SOT_SMD:SOT-23-6","TPS54302DDCR","C311983","4.5-28 V input, 3 A synchronous step-down converter, 400 kHz, SOT-23-6"

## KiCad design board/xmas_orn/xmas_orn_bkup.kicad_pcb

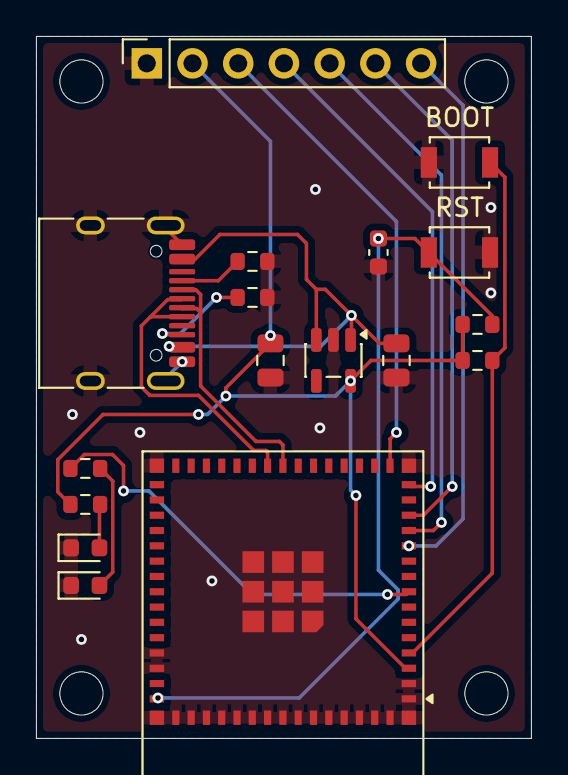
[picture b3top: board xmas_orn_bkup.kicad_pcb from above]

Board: 2 copper layers, 27.5 x 39.0 mm, 17 parts (0 on the bottom side), 17 nets.

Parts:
BOOT: BOOT; SW_SPST_B3U-1000P
C1, C2: 10uF; C_0805_2012Metric
C3: 1uF; C_0603_1608Metric
D1, D2: LED; LED_0603_1608Metric
J1: Conn_01x07_Socket; PinSocket_1x07_P2.54mm_Vertical
J3: USB_C_Receptacle_USB2.0_16P; USB_C_Receptacle_HRO_TYPE-C-31-M-12
R1, R2: 5.1k; R_0603_1608Metric
R3, R4: 10k; R_0603_1608Metric
R5: 2k; R_0603_1608Metric
R6: 470; R_0603_1608Metric
RST: RST; SW_SPST_B3U-1000P
U1: ESP32-S3-MINI-1; ESP32-S2-MINI-1
U2: TLV75733PDBV; SOT-23-5

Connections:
/EN: C3.1, R3.2, RST.2, U1.45 (EN)
/GPIO0: BOOT.2, R4.2, U1.4 (IO0)
/GPIO4: R6.2, U1.8 (IO4)
/LCD_BLK: J1.7, U1.11 (IO7)
/LCD_DC: J1.6, U1.13 (IO9)
/LCD_MOSI: J1.4, U1.15 (IO11)
/LCD_RST: J1.5, U1.12 (IO8)
/LCD_SCLK: J1.3, U1.16 (IO12)
/USB+: J3.A6 (D+), J3.B6 (D+), U1.24 (USB_D+)
/USB-: J3.A7 (D-), J3.B7 (D-), U1.23 (USB_D-)
/VCC: C2.1, J1.2, R3.1, R4.1, R5.1, U1.3 (3V3), U2.5 (OUT)
/VIN: C1.1, J3.A4 (VBUS), J3.A9 (VBUS), J3.B4 (VBUS), J3.B9 (VBUS), U2.1 (IN), U2.3 (EN)
GND: BOOT.1, C1.2, C2.2, C3.2, D1.1 (K), D2.1 (K), J1.1, J3.A1 (GND), J3.A12 (GND), J3.B1 (GND), J3.B12 (GND), J3.SH (SHIELD), R1.1, R2.2, RST.1, U1.1 (GND), U1.2 (GND), U1.42 (GND), U1.43 (GND), U1.46 (GND), U1.47 (GND), U1.48 (GND), U1.49 (GND), U1.50 (GND), U1.51 (GND), U1.52 (GND), U1.53 (GND), U1.54 (GND), U1.55 (GND), U1.56 (GND), U1.57 (GND), U1.58 (GND), U1.59 (GND), U1.60 (GND), U1.61 (GND), U1.62 (GND), U1.63 (GND), U1.64 (GND), U1.65 (GND), U2.2 (GND)
unnamed: D1.2 (A), R5.2
unnamed: D2.2 (A), R6.1
unnamed: J3.A5 (CC1), R1.2
unnamed: J3.B5 (CC2), R2.1

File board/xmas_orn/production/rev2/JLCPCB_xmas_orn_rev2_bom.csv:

Designator,Footprint,Quantity,Value,LCSC Part #
"C1, C2",0805,2,10uF,CL21A106KOQNNNE
C3,0603,1,1uF,CL10A105KA8NNNC
"D1, D2",0603,2,LED,19-217/R6C-AL1M2VY/6T
"D3, D4",SOD-123,2,B5819W,C8598
J1,PinSocket_1x07_P2.54mm_Vertical,1,Conn_01x07_Socket,HX PM2.54-1x7P ZC-Y
J3,USB_C_Receptacle_HRO_TYPE-C-31-M-12,1,USB_C_Receptacle_USB2.0_16P,TYPE-C-31-M-12
"R1, R2",0603,2,5.1k,RC0603FR-075K1L
"R3, R4",0603,2,10k,AC0603JR-0710KL
R5,0603,1,2k,RC0603JR-072KL
R6,0603,1,470,RC0603FR-07470RL
SW1,SW_SPST_B3U-1000P,1,RST,B3U-1000P
SW2,SW_SPST_B3U-1000P,1,BOOT,B3U-1000P
U1,ESP32-S3-WROOM-1,1,ESP32-S3-WROOM-1,C2913202
U2,SOT-23-5,1,TLV75733PDBV,TLV75733PDBVR-MS

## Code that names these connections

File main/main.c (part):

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static const char *TAG = "xmas_model";

#define LCD_HOST                SPI2_HOST
#define PIN_LCD_SCLK            12
#define PIN_LCD_MOSI            11
#define PIN_LCD_CS              -1
#define PIN_LCD_DC              9
#define PIN_LCD_RST             8
#define PIN_LCD_BLK             7
#define PIN_PULSE               4
/*
 * BOOT, the only button on this board.
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        .clk_cfg = LEDC_AUTO_CLK,
    };
    ledc_channel_config_t channel = {
        .gpio_num = PIN_LCD_BLK,
        .speed_mode = LCD_BL_LEDC_MODE,
        .channel = LCD_BL_LEDC_CHANNEL,
        .timer_sel = LCD_BL_LEDC_TIMER,
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static void lcd_init(void)
{
    spi_bus_config_t bus_cfg = {
        .sclk_io_num = PIN_LCD_SCLK,
        .mosi_io_num = PIN_LCD_MOSI,
        .miso_io_num = -1,
        .quadwp_io_num = -1,
        .quadhd_io_num = -1,
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    ESP_ERROR_CHECK(spi_bus_initialize(LCD_HOST, &bus_cfg, SPI_DMA_CH_AUTO));

    esp_lcd_panel_io_spi_config_t io_cfg = {
        .dc_gpio_num = PIN_LCD_DC,
        .cs_gpio_num = PIN_LCD_CS,
        .pclk_hz = LCD_PIXEL_CLOCK_HZ,
        .lcd_cmd_bits = 8,
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    }

    esp_lcd_panel_dev_config_t panel_cfg = {
        .reset_gpio_num = PIN_LCD_RST,
        .rgb_ele_order = LCD_RGB_ELEMENT_ORDER_RGB,
        .bits_per_pixel = 16,
    };
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
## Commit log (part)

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2026-06-10 Order Placed: JLCPCD
2026-06-11 rendering model 0
2026-06-11 main
2026-06-17 working with pcb
2026-06-17 readme
